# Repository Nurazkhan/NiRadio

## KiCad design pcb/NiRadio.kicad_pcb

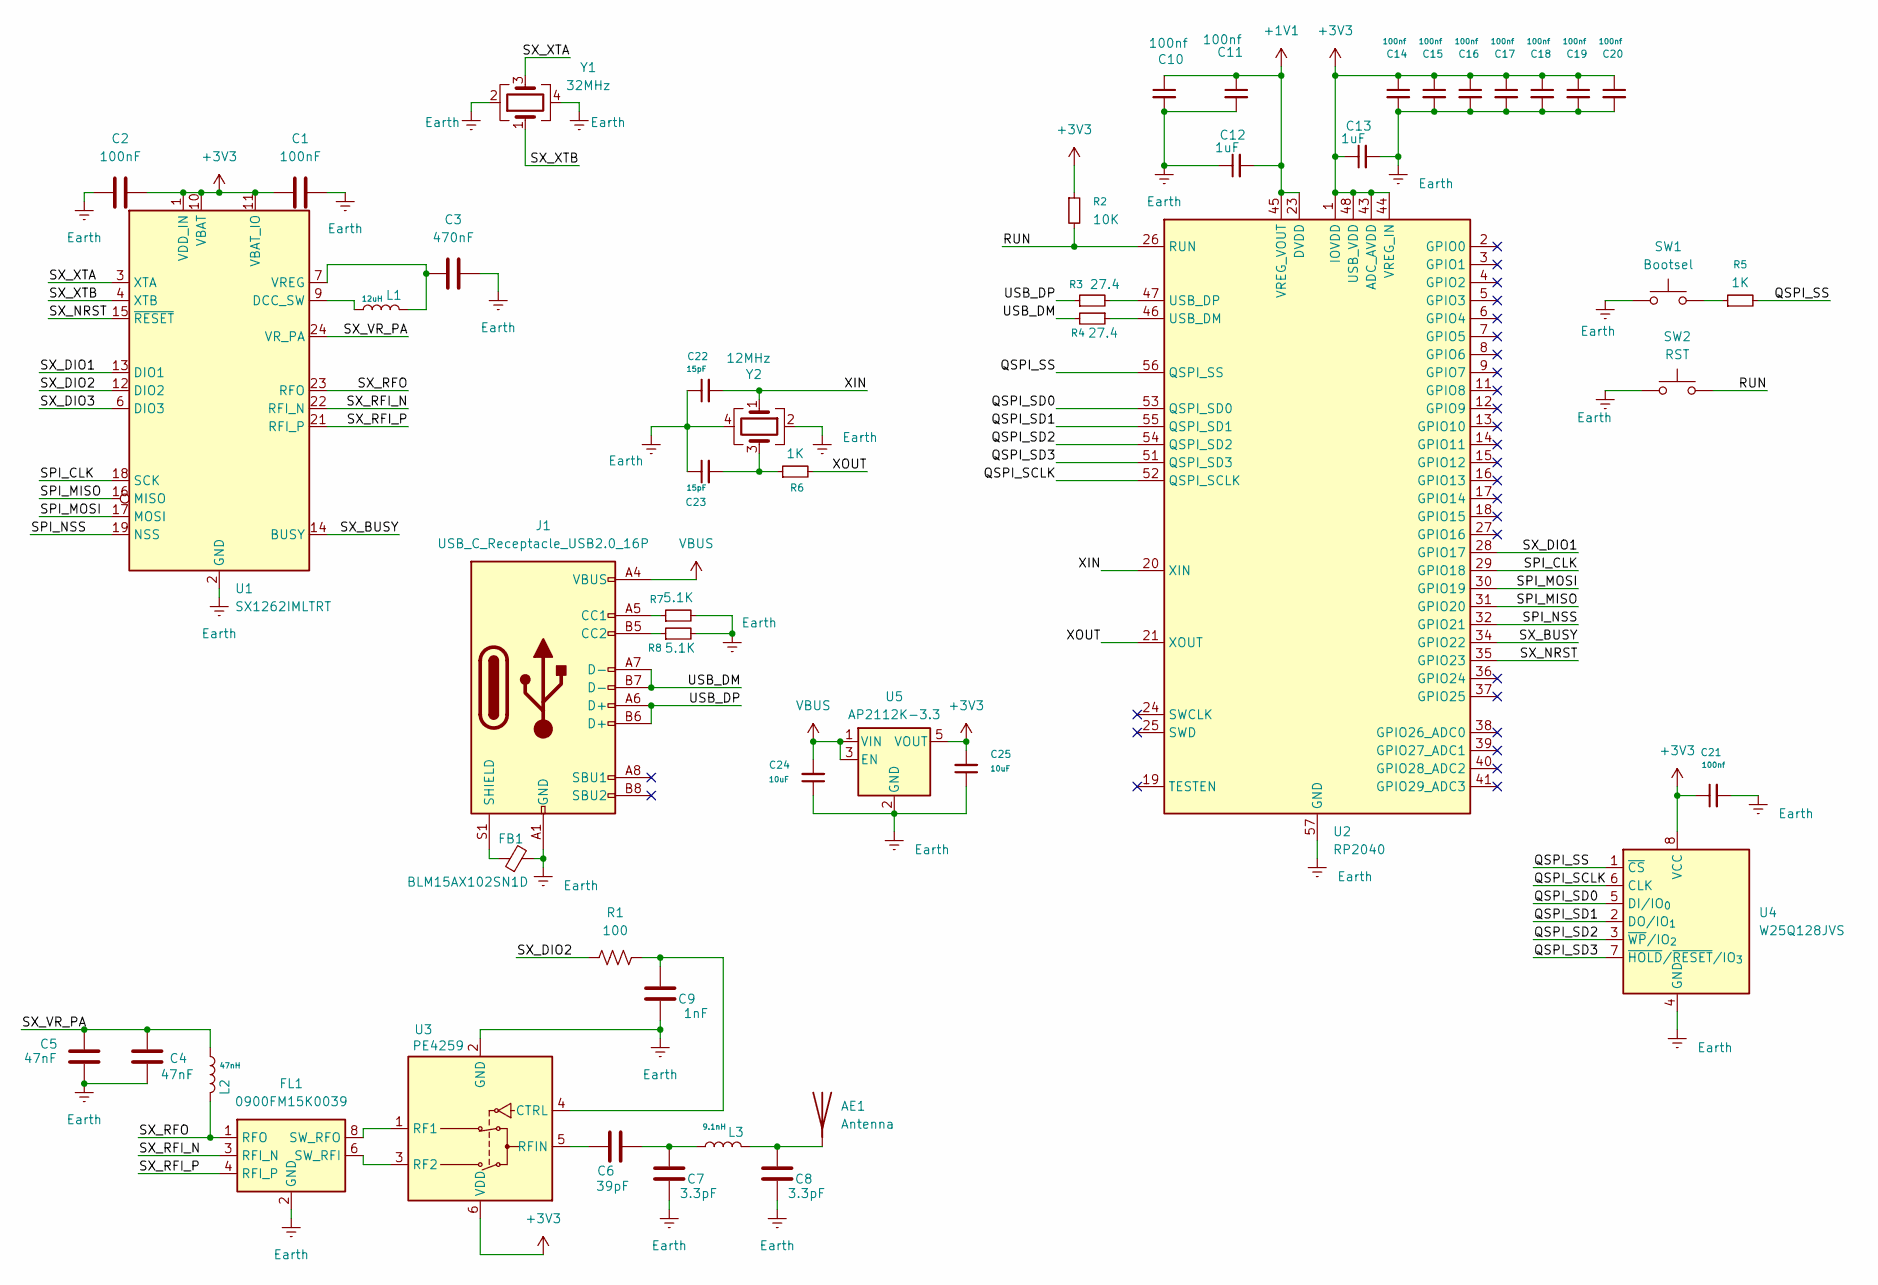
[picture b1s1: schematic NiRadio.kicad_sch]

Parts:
AE1: Antenna; PinSocket_1x01_P2.54mm_Vertical
C1, C2: 100nF; C_0402_1005Metric
C3: 470nF; C_0402_1005Metric
C4, C5: 47nF; C_0402_1005Metric
C6: 39pF; C_0402_1005Metric
C7, C8: 3.3pF; C_0402_1005Metric
C9: 1nF; C_0402_1005Metric
C10, C11, C14, C15, C16, C17, C18, C19, C20, C21: 100nf; C_0402_1005Metric
C12, C13: 1uF; C_0402_1005Metric
C22, C23: 15pF; C_0402_1005Metric
C24, C25: 10uF; C_0402_1005Metric
FB1: BLM15AX102SN1D; L_0402_1005Metric
FL1: 0900FM15K0039; Balun_Johanson_0900FM15K0039
J1: USB_C_Receptacle_USB2.0_16P; USB_C_Receptacle_GCT_USB4105-xx-A_16P_TopMnt_Horizontal
L1: 12uH; L_0402_1005Metric
L2: 47nH; L_0402_1005Metric
L3: 9.1nH; L_0402_1005Metric
R1: 100; R_0402_1005Metric
R2: 10K; R_0402_1005Metric
R3, R4: 27.4; R_0402_1005Metric
R5, R6: 1K; R_0402_1005Metric
R7, R8: 5.1K; R_0402_1005Metric
SW1: Bootsel; SW_Tactile_SPST_NO_Straight_CK_PTS636Sx25SMTRLFS
SW2: RST; SW_Tactile_SPST_NO_Straight_CK_PTS636Sx25SMTRLFS
U1: SX1262IMLTRT; QFN-24-1EP_4x4mm_P0.5mm_EP2.6x2.6mm
U2: RP2040; QFN-56-1EP_7x7mm_P0.4mm_EP3.2x3.2mm
U3: PE4259; SOT-363_SC-70-6
U4: W25Q128JVS; SOIC-8_5.3x5.3mm_P1.27mm
U5: AP2112K-3.3; SOT-23-5
Y1: 32MHz; Crystal_SMD_3225-4Pin_3.2x2.5mm
Y2: 12MHz; Crystal_SMD_Abracon_ABM8G-4Pin_3.2x2.5mm

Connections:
+1V1: C10.1, C11.1, C12.2, U2.23 (DVDD), U2.45 (VREG_VOUT), U2.50 (DVDD)
+3V3: C1.1, C2.2, C13.1, C14.1, C15.1, C16.1, C17.1, C18.1, C19.1, C20.1, C21.1, C25.2, R2.1, U1.1 (VDD_IN), U1.10 (VBAT), U1.11 (VBAT_IO), U2.1 (IOVDD), U2.10 (IOVDD), U2.22 (IOVDD), U2.33 (IOVDD), U2.42 (IOVDD), U2.43 (ADC_AVDD), U2.44 (VREG_IN), U2.48 (USB_VDD), U2.49 (IOVDD), U3.6 (VDD), U4.8 (VCC), U5.5 (VOUT)
/QSPI_SCLK: U2.52 (QSPI_SCLK), U4.6 (CLK)
/QSPI_SD0: U2.53 (QSPI_SD0), U4.5 (DI/IO_{0})
/QSPI_SD1: U2.55 (QSPI_SD1), U4.2 (DO/IO_{1})
/QSPI_SD2: U2.54 (QSPI_SD2), U4.3 (~WP/IO_{2})
/QSPI_SD3: U2.51 (QSPI_SD3), U4.7 (~HOLD/~RESET/IO_{3})
/QSPI_SS: R5.2, U2.56 (QSPI_SS), U4.1 (~CS)
/RUN: R2.2, SW2.2, U2.26 (RUN)
/SPI_CLK: U1.18 (SCK), U2.29 (GPIO18)
/SPI_MISO: U1.16 (MISO), U2.31 (GPIO20)
/SPI_MOSI: U1.17 (MOSI), U2.30 (GPIO19)
/SPI_NSS: U1.19 (NSS), U2.32 (GPIO21)
/SX_BUSY: U1.14 (BUSY), U2.34 (GPIO22)
/SX_DIO1: U1.13 (DIO1), U2.28 (GPIO17)
/SX_DIO2: R1.2, U1.12 (DIO2)
/SX_DIO3: U1.6 (DIO3)
/SX_NRST: U1.15 (~RESET), U2.35 (GPIO23)
/SX_RFI_N: FL1.3 (RFI_N), U1.22 (RFI_N)
/SX_RFI_P: FL1.4 (RFI_P), U1.21 (RFI_P)
/SX_RFO: FL1.1 (RFO), L2.2, U1.23 (RFO)
/SX_VR_PA: C4.2, C5.2, L2.1, U1.24 (VR_PA)
/SX_XTA: U1.3 (XTA), Y1.3
/SX_XTB: U1.4 (XTB), Y1.1
/USB_DM: J1.A7 (D-), J1.B7 (D-), R4.2
/USB_DP: J1.A6 (D+), J1.B6 (D+), R3.1
/XIN: C22.2, U2.20 (XIN), Y2.1
/XOUT: R6.2, U2.21 (XOUT)
Earth: C1.2, C2.1, C3.2, C4.1, C5.1, C7.1, C8.1, C9.1, C10.2, C11.2, C12.1, C13.2, C14.2, C15.2, C16.2, C17.2, C18.2, C19.2, C20.2, C21.2, C22.1, C23.1, C24.1, C25.1, FB1.2, FL1.2 (GND), FL1.5 (GND), FL1.7 (GND), FL1.9 (GND), FL1.10 (GND), J1.A1 (GND), J1.A12 (GND), J1.B1 (GND), J1.B12 (GND), R7.2, R8.2, SW1.1, SW2.1, U1.2 (GND), U1.5 (GND), U1.8 (GND), U1.20 (GND), U1.25 (GND), U2.57 (GND), U3.2 (GND), U4.4 (GND), U5.2 (GND), Y1.2, Y1.4, Y2.2, Y2.4
unnamed: AE1.1 (A), C8.2, L3.2
unnamed: C6.2, C7.2, L3.1
unnamed: C23.2, R6.1, Y2.3
unnamed: FL1.6 (SW_RFI), U3.3 (RF2)
unnamed: FL1.8 (SW_RFO), U3.1 (RF1)
unnamed: J1.A5 (CC1), R7.1
unnamed: J1.B5 (CC2), R8.1
unnamed: FB1.1, J1.S1 (SHIELD)
unnamed: R5.1, SW1.2
unnamed: L1.1, U1.9 (DCC_SW)
unnamed: C3.1, L1.2, U1.7 (VREG)
unnamed: R4.1, U2.46 (USB_DM)
unnamed: R3.2, U2.47 (USB_DP)
unnamed: C9.2, R1.1, U3.4 (CTRL)
unnamed: C6.1, U3.5 (RFIN)
VBUS: C24.2, J1.A4 (VBUS), J1.A9 (VBUS), J1.B4 (VBUS), J1.B9 (VBUS), U5.1 (VIN), U5.3 (EN)

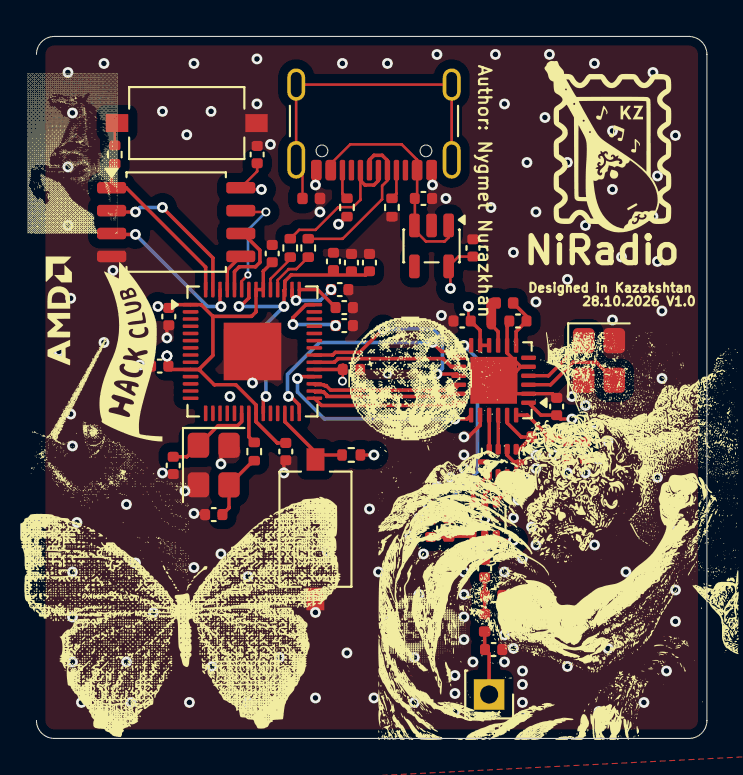
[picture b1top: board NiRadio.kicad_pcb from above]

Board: 4 copper layers, 37.2 x 39.0 mm, 49 parts (0 on the bottom side), 44 nets.

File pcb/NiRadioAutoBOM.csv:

"Id";"Designator";"Footprint";"Quantity";"Designation";"Supplier and ref";
1;"C13,C12";"C_0402_1005Metric";2;"1uF";;;
2;"C9";"C_0402_1005Metric";1;"1nF";;;
3;"C15,C14,C10,C19,C18,C20,C17,C21,C11,C16";"C_0402_1005Metric";10;"100nf";;;
4;"U3";"SOT-363_SC-70-6";1;"PE4259";;;
5;"C25,C24";"C_0402_1005Metric";2;"10uF";;;
6;"L2";"L_0402_1005Metric";1;"47nH";;;
7;"R2";"R_0402_1005Metric";1;"10K";;;
8;"SW1";"SW_Tactile_SPST_NO_Straight_CK_PTS636Sx25SMTRLFS";1;"Bootsel";;;
9;"U2";"QFN-56-1EP_7x7mm_P0.4mm_EP3.2x3.2mm";1;"RP2040";;;
10;"Y2";"Crystal_SMD_Abracon_ABM8G-4Pin_3.2x2.5mm";1;"12MHz";;;
11;"C7,C8";"C_0402_1005Metric";2;"3.3pF";;;
12;"C5,C4";"C_0402_1005Metric";2;"47nF";;;
13;"R5,R6";"R_0402_1005Metric";2;"1K";;;
14;"C2,C1";"C_0402_1005Metric";2;"100nF";;;
15;"SW2";"SW_Tactile_SPST_NO_Straight_CK_PTS636Sx25SMTRLFS";1;"RST";;;
16;"AE1";"PinSocket_1x01_P2.54mm_Vertical";1;"Antenna";;;
17;"C6";"C_0402_1005Metric";1;"39pF";;;
18;"U4";"SOIC-8_5.3x5.3mm_P1.27mm";1;"W25Q128JVS";;;
19;"L3";"L_0402_1005Metric";1;"9.1nH";;;
20;"R4,R3";"R_0402_1005Metric";2;"27.4";;;
21;"FB1";"L_0402_1005Metric";1;"BLM15AX102SN1D";;;
22;"U1";"QFN-24-1EP_4x4mm_P0.5mm_EP2.6x2.6mm";1;"SX1262IMLTRT";;;
23;"C22,C23";"C_0402_1005Metric";2;"15pF";;;
24;"Y1";"Crystal_SMD_3225-4Pin_3.2x2.5mm";1;"32MHz";;;
25;"J1";"USB_C_Receptacle_GCT_USB4105-xx-A_16P_TopMnt_Horizontal";1;"USB_C_Receptacle_USB2.0_16P";;;
26;"L1";"L_0402_1005Metric";1;"12uH";;;
27;"FL1";"Balun_Johanson_0900FM15K0039";1;"0900FM15K0039";;;
28;"R8,R7";"R_0402_1005Metric";2;"5.1K";;;
29;"R1";"R_0402_1005Metric";1;"100";;;
30;"C3";"C_0402_1005Metric";1;"470nF";;;
31;"U5";"SOT-23-5";1;"AP2112K-3.3";;;
